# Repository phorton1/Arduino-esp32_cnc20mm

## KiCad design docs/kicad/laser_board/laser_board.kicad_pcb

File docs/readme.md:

# CNC Machine based on 20mm Stainless Steel Tubes

**Home** --
**[Design](design.md)** --
**[Details](details.md)** --
**[Electronics](electronics.md)** --
**[Box](box.md)** --
**[Spindle](spindle.md)** --
**[Y-Axis](y_axis.md)** --
**[Table](table.md)** --
**[Build](build.md)** --
**[Laser](laser.md)** --
**[Accessories](accessories.md)** --
**[Software](software.md)** --
**[Notes](notes.md)** --
**[Projects](projects.md)**

After completing the [2nd 3018](https://github.com/phorton1/Arduino-esp32_cnc3018/blob/master/docs/version2.md)
[cnc_machine](https://github.com/phorton1/Arduino-esp32_cnc3018), I felt I was
ready to attempt to make a larger machine.  I wanted to be able to cut 4x8 or 4x4 sheets
of plywood.

The belt driven cnc20mm machine is based on stainless steel 20mm tubes and 3D printed linear bearings that
utilize small inexpensive ball bearings.
It uses these items because it is prohibitively expensive to for me to ship large heavy items
like *aliminum extrusions* and *real linear bearings* and *linear drives* to my build location.
The biggest and heaviest parts are the lumber and stainless steel tubes,
both of which are available lococally.

The version I ended up building will cut a little bigger than 4x4 feet (51x50 inches).

It uses Nema23 motors.  These motors are larger than my previous machines
and so it requires larger, higher power, external controller boards.

## Outline of Documentation

On these pages I will *describe* and *show* the following:

- the basic mechanical **[Design](design.md)** of the machine
- some design **[Details](details.md)**, including Drag Chains, Connectors, etc
- the **[Electronics](electronics.md)** *Schematic* and *PCB* (Printed Circuit Board)
- the main **[Controller Box](box.md)**
- the separate **[Spindle](spindle.md)** controller box
- the *initial build* of the **[Y-Axis](y_axis.md)**
- constructing the **[Table](table.md)** (furniture) to support the machine
- assembling and **[Building](build.md)** the *actual* machine
- upgrading the **[Laser](laser.md)** from 500mw to a whopping **10W diode laser**
- adding **[Accessories](accessories.md)** including the *Spindle Controller* and *Vacuum* System
- installed and understanding the **[FluidNC Software](software.md)** for the *ESP32*
- implementation and historical **[Notes](notes.md)**
- and, finally, a few early **[Wooden Projects](projects.md)** that were made with the machine

## Materials available in this Repository

## Credits

R38 18x37 Drag Chain Model from Darko Saric Lukendic https://grabcad.com/library/cable-chain-18x37-1

## License

## Please Also See

- cnc3018
- vMachine
- FluidNC
- FluidNC_UI
- FluidNC_Extensions

**Next** - The basic [**Mechanical Design**](design.md) of the machine ...

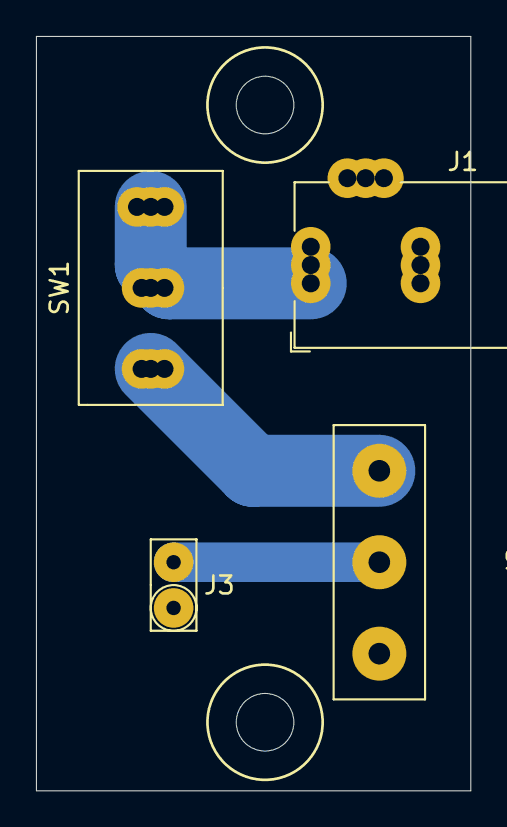
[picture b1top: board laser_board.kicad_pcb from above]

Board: 2 copper layers, 24.1 x 41.9 mm, 4 parts (0 on the bottom side), 4 nets.

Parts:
J1: Barrel_Jack_Switch; myBarrelJack
J2: Conn_01x03; Phoenix5.08x3
J3: Conn_01x02; my2pin
SW1: SW_SPDT; mySwitchToggleSPDT

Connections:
unnamed: J1.1, SW1.1, SW1.2
unnamed: J1.2, J2.3, J3.1
unnamed: J2.1, SW1.3
unnamed: J2.2, J3.2

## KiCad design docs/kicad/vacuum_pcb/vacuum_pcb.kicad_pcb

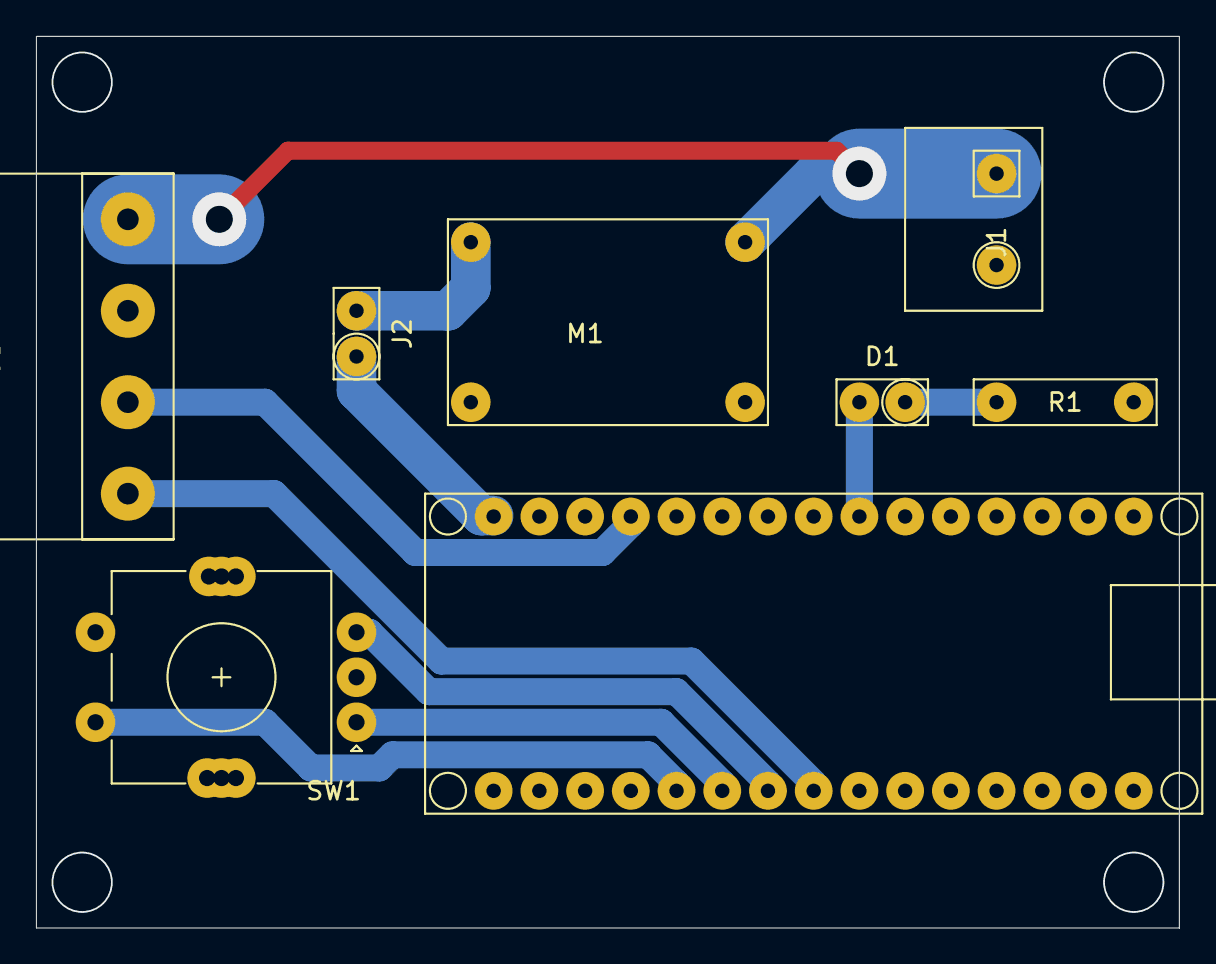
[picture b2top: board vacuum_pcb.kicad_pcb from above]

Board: 2 copper layers, 63.5 x 49.5 mm, 8 parts (0 on the bottom side), 11 nets.

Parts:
D1: LED; my2pin
J1: 24v; mySkip1
J2: 5V Jumper; my2pin
J3: Conn_01x04; big_4pin
M1: BUCK01
R1: 220; myResistor
SW1: RE; RotaryEncoder
U1: ARDUINO_NANO

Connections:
GND: J1.2, J3.3, M1.1, M1.2, R1.2, SW1.C, SW1.S2, U1.2, U1.27
unnamed: D1.1, R1.1
unnamed: D1.2, U1.9
unnamed: J1.1, J3.4, M1.4
unnamed: J2.1, U1.1
unnamed: J2.2, M1.3
unnamed: J3.1, U1.23
unnamed: J3.2, U1.4
unnamed: SW1.A, U1.25
unnamed: SW1.B, U1.24
unnamed: SW1.S1, U1.26

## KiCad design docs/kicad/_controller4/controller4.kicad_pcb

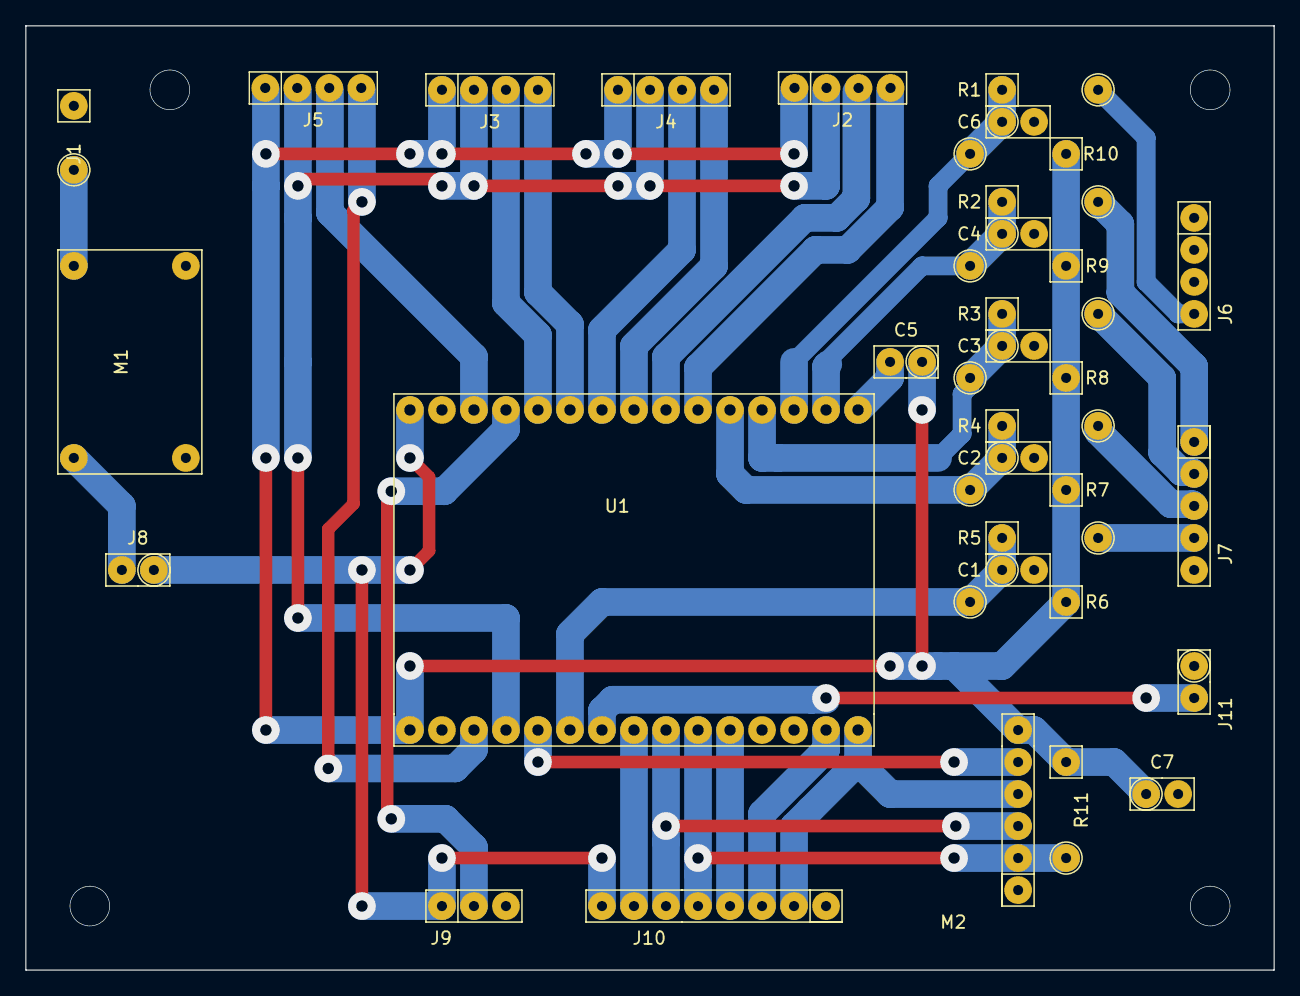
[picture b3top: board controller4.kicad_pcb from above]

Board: 2 copper layers, 99.1 x 74.9 mm, 32 parts (0 on the bottom side), 34 nets.

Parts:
C1, C2, C3, C4, C6: 100nf; my2pin
C5: 10uF; my2pin
C7: 220uf 10V; my2pin
J1: 24V; mySkip1
J2: Z_AXIS; my4pin
J3: A_AXIS; my4pin
J4: Y_AXIS; my4pin
J5: X_AXIS; my4pin
J6: PROBE; my4pin
J7: LIMITS; my5Pin
J8: USB 5V; my2pin
J9: LEDS; my3pin
J10: DISPLAY; my8Pin
J11: PWM; my2pin
M1: BUCK01
M2: SD CARD; my6Pin
R1, R2, R3, R4, R5: 100; mySkip2
R6, R7, R8, R9, R10, R11: 10K; mySkip2
U1: ESP32_DEV_0; ESP32-DEV_0

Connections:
+3V3: C5.1, C7.1, J2.1, J3.1, J4.1, J5.1, M2.6, R6.1, R7.1, R8.1, R9.1, R10.1, R11.1, U1.30
+5V: J8.1, J9.1, J10.8, U1.1
A_DIR: J3.3, U1.5
A_STEP: J3.4, U1.6
A_SW: C3.1, R3.1, R8.2, U1.12
GND: C1.2, C2.2, C3.2, C4.2, C6.2, C7.2, J1.1, J7.5, J9.3, J10.1, J11.1, M1.1, M1.2, M2.1, U1.2, U1.29
LED: J9.2, U1.4
MCLK: J10.6, M2.3, U1.22
MISO: J10.5, M2.2, R11.2, U1.21
MOSI: J10.2, M2.4, U1.16
unnamed: C5.2, U1.15
unnamed: J1.2, M1.4
unnamed: J6.4, R1.2
unnamed: J7.1, R2.2
unnamed: J7.2, R3.2
unnamed: J7.3, R4.2
unnamed: J7.4, R5.2
unnamed: J8.2, M1.3
PROBE_SW: C6.1, R1.1, R10.2, U1.13
PWM: J11.2, U1.24
SD_CS: M2.5, U1.26
STEP_EN: J2.2, J3.2, J4.2, J5.2, U1.27
TFT_CS: J10.3, U1.17
TFT_DC: J10.4, U1.20
TOUCH_CS: J10.7, U1.23
X_DIR: J2.3, U1.9
X_STEP: J2.4, U1.10
X_SW: C1.1, R5.1, R6.2, U1.25
Y_DIR: J4.3, U1.7
Y_STEP: J4.4, U1.8
Y_SW: C2.1, R4.1, R7.2, U1.11
Z_DIR: J5.3, U1.3
Z_STEP: J5.4, U1.28
Z_SW: C4.1, R2.1, R9.2, U1.14

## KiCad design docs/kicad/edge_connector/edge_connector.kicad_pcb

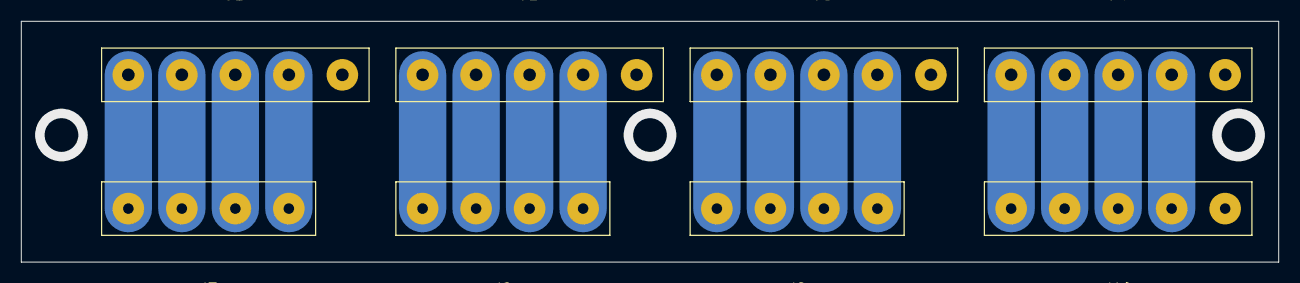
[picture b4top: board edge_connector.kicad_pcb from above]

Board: 2 copper layers, 119.4 x 22.9 mm, 8 parts (0 on the bottom side), 17 nets.

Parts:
J1, J2, J3, J4, J10: Conn_01x05; big_5pin
J7, J8, J9: Conn_01x04; big_4pin

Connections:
GND: J1.5, J2.5, J3.5, J4.5, J10.1
unnamed: J1.1, J7.4
unnamed: J1.2, J7.3
unnamed: J1.3, J7.2
unnamed: J1.4, J7.1
unnamed: J2.1, J8.4
unnamed: J2.2, J8.3
unnamed: J2.3, J8.2
unnamed: J2.4, J8.1
unnamed: J3.1, J9.4
unnamed: J3.2, J9.3
unnamed: J3.3, J9.2
unnamed: J3.4, J9.1
unnamed: J4.4, J10.2
unnamed: J4.3, J10.3
unnamed: J4.2, J10.4
unnamed: J4.1, J10.5

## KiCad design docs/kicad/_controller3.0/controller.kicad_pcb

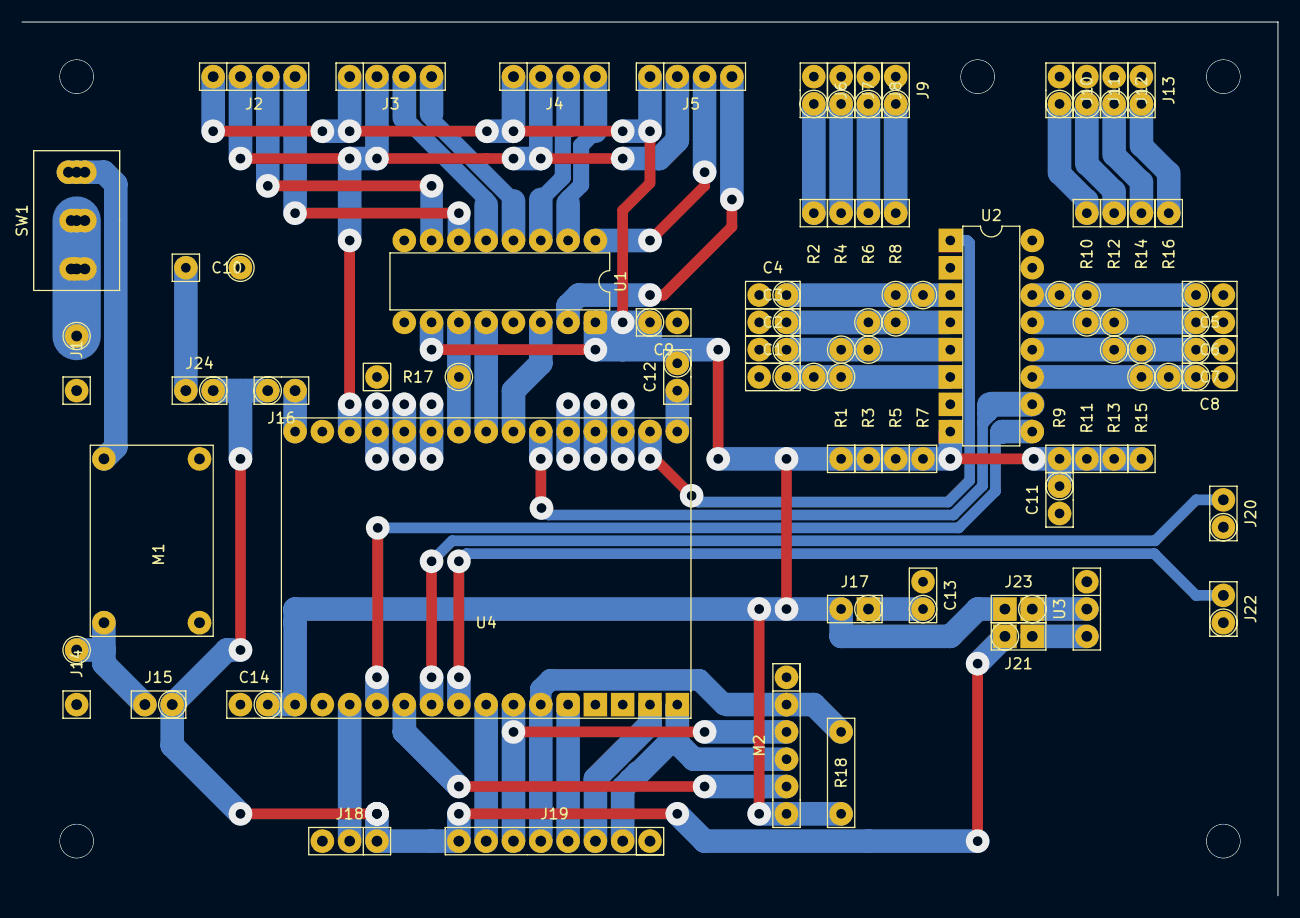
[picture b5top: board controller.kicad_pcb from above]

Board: 2 copper layers, 116.8 x 81.3 mm, 63 parts (0 on the bottom side), 53 nets.

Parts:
C1, C2, C3, C4, C5, C6, C7, C8, C9, C11, C14: 100nf; my2pin
C10: 330uf 50v; mySkip1
C12: 10uF; my2pin
C13: 220uf 10V; my2pin
J1: 24V; mySkip1
J2: X_AXIS; my4pin
J3: A_AXIS; my4pin
J4: Y_AXIS; my4pin
J5: Z_AXIS; my4pin
J6: X_ZERO; my2pin
J7: X_LIM; my2pin
J8: Y_ZERO; my2pin
J9: Y_LIM; my2pin
J10: Z_ZERO; my2pin
J11: Z_LIM; my2pin
J12: PROBE; my2pin
J13: UNUSED; my2pin
J14: 5V; mySkip1
J15: EXT 5V; my2pin
J16: USB 5V; my2pin
J17: CAP3V; my2pin
J18: WS2812B Strip; my3pin
J19: Display; my8Pin
J20: PWM_1A; my2pin
J21: REG5V; my2pin
J22: PWM_2A; my2pin
J23: REG3V; my2pin
J24: CAP5V; my2pin
M1: BUCK01
M2: SD_TYP0; my6Pin
R1, R15, R17: 10K; mySkip2
R2, R16: 100; mySkip5
R3, R13: 10K; mySkip3
R4, R14: 100; mySkip4
R5, R11: 10K; mySkip4
R6, R12: 100; mySkip3
R7, R9: 10K; mySkip5
R8, R10: 100; mySkip2
R18: 10K; myResistor
SW1: POWER; SW_DPDT_BLUE_LEVER
U1: 74HC595; myDip16
U2: 74HC165; myDip16
U3: LM1117; my3pin
U4: ESP32_DEV_0; ESP32-DEV_0

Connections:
+3V3: C9.1, C11.1, C12.1, C14.1, J2.1, J3.1, J4.1, J5.1, J17.2, J23.2, M2.6, R1.1, R3.1, R5.1, R7.1, R9.1, R11.1, R13.1, R15.1, R18.1, U1.10, U1.16, U2.8, U4.30
+5V: J15.1, J16.1, J18.1, J19.8, J21.1, J24.1
+24V: M1.4, SW1.1
A_DIR: J3.3, U1.5
A_STEP: J3.4, U1.4
GND: C1.2, C2.2, C3.2, C4.2, C5.2, C6.2, C7.2, C8.2, C9.2, C10.2, C11.2, C13.2, C14.2, J1.1, J6.2, J7.2, J8.2, J9.2, J10.2, J11.2, J12.2, J13.2, J14.1, J18.3, J19.1, J20.1, J22.1, M1.1, M1.2, M2.1, R17.1, U1.8, U1.13, U2.2, U2.7, U2.16, U3.1, U4.2, U4.29
I2S_BCK: R17.2, U1.11, U4.7
I2S_DATA: U1.14, U4.9
I2S_WS: U1.12, U4.8
LED: J18.2, U4.28
MCLK: J19.6, M2.3, U4.22
MISO: J19.5, M2.2, R18.2, U4.21
MOSI: J19.2, M2.4, U4.16
unnamed: C1.1, R1.2, R2.2, U2.6
unnamed: C2.1, R3.2, R4.2, U2.5
unnamed: C3.1, R5.2, R6.2, U2.4
unnamed: C4.1, R7.2, R8.2, U2.3
unnamed: C5.1, R9.2, R10.2, U2.14
unnamed: C6.1, R11.2, R12.2, U2.13
unnamed: C7.1, R13.2, R14.2, U2.12
unnamed: C8.1, R15.2, R16.2, U2.11
unnamed: C10.1, J24.2
unnamed: C12.2, U4.15
unnamed: C13.1, J17.1
unnamed: J1.2, SW1.2, SW1.3
unnamed: J6.1, R2.1
unnamed: J7.1, R4.1
unnamed: J8.1, R6.1
unnamed: J9.1, R8.1
unnamed: J10.1, R10.1
unnamed: J11.1, R12.1
unnamed: J12.1, R14.1
unnamed: J13.1, R16.1
unnamed: J14.2, J15.2, M1.3
unnamed: J16.2, U4.1
unnamed: J21.2, U3.3
unnamed: J23.1, U3.2
PWM_1: J20.2, U4.25
PWM_2: J22.2, U4.24
SD_CS: M2.5, U4.26
STEP_EN: J2.2, J3.2, J4.2, J5.2, U4.3
SW_CLK: U2.10, U4.10
SW_DATA: U2.1, U4.14
SW_LATCH: U2.9, U4.27
TFT_CS: J19.3, U4.17
TFT_DC: J19.4, U4.20
TOUCH_CS: J19.7, U4.23
X_DIR: J2.3, U1.7
X_STEP: J2.4, U1.6
Y_DIR: J4.3, U1.3
Y_STEP: J4.4, U1.2
Z_DIR: J5.3, U1.1
Z_STEP: J5.4, U1.15

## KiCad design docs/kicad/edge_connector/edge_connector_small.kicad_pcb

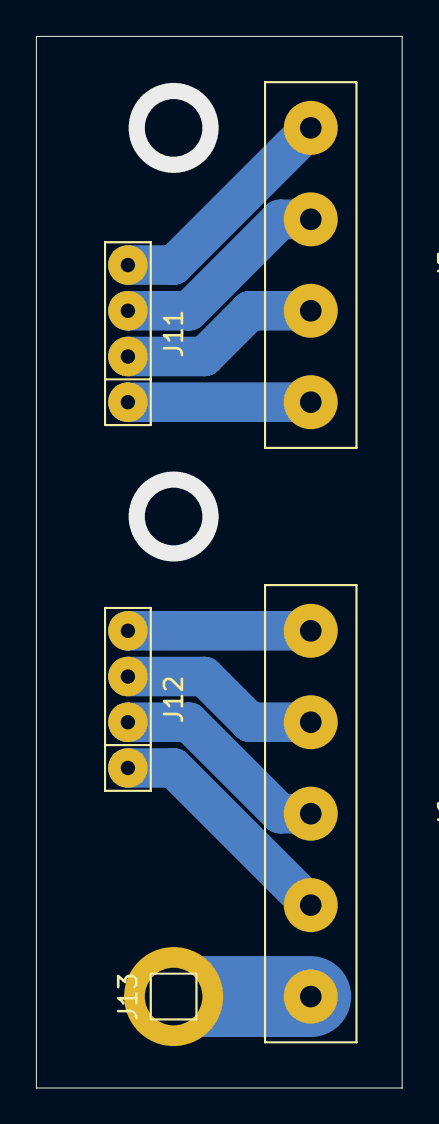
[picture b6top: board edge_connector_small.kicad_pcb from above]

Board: 2 copper layers, 20.3 x 58.4 mm, 5 parts (0 on the bottom side), 9 nets.

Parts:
J5: Conn_01x04; big_4pin
J6: Conn_01x05; big_5pin
J11, J12: Conn_01x04; my4pin
J13: Conn_01x01; my1pin

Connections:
unnamed: J5.4, J11.1
unnamed: J5.3, J11.2
unnamed: J5.2, J11.3
unnamed: J5.1, J11.4
unnamed: J6.4, J12.1
unnamed: J6.3, J12.2
unnamed: J6.2, J12.3
unnamed: J6.1, J12.4
unnamed: J6.5, J13.1

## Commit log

2022-03-28 initial commit (from branch)
2022-03-28 rename files, initial build
2022-04-10 renamed config_v3_i2s0.yaml to config_cnc20mm.yaml, noting that the laser and non-laser are the same (as long as I have no PWM spindle)
2022-04-10 sanity checking after completing most circuit boards
2022-04-13 added spindle connector kicad stuff
2022-04-13 added stepper wiring and full cnc pin_history (comments only)
2022-04-14 remove vTaskDelay that was kludge for logging synchronization
2022-04-14 comments only
2022-04-15 implement FluidNC_UI driver/size/rotation API - rename tft calibration data files
2022-04-15 Implement LIMIT_PINS and REVERSE_PIXELS
2022-04-18 Initial readme.md, pics, and two youtube videos
2022-04-18 readme
2022-05-19 change big edge connector to 5 pin (grounds for steppers)
2022-05-23 added tasks.txt - analsysis of running tasks
2022-07-03 update prefs for build
2022-07-03 use 32bit limit variables, set XYAZ orcer
2022-07-03 final INITIAL WORKING CNC20MM
2022-07-05 added laser_board
2022-07-05 cleanup configs (add Laser)
2022-07-05 updated preferences.txt
2022-07-05 correct probe pin
2022-07-21 added #ifdef'd out WEAK_LINK display() method
2022-07-29 Turned off DEBUG_PIXELS define
2022-07-29 sdded disasm_cmd.bat to get disassembly listings for debugging
2022-07-29 changed (fixed) WEAK_LINK display() method (though it still doesnt work with UGS)
2022-07-29 changed PWM_HZ to 5000 which fixed some laser missing bands
2022-08-09 new controller4 (v4) circuit board
2022-08-09 NEW v4 CONFIG FILE
2022-08-10 add v4 comments
2022-08-21 added ToolChange macro files
2022-08-21 added comments on how to run toolChange macros from SPIFFS
2022-08-21 added setting_z_height.txt document
2022-08-24 better TOOL CHANGE macros - got rid of analysis
2022-08-24 lower homing feed rates
2022-12-12 updated ground plane while reviewing docs and pcbs
2023-03-21 make the current v4 configuration the default config.yaml
2023-04-16 moved to /bat
2023-07-17 docs - start writing actual documentation
2023-07-17 doc - typos
2023-07-20 docs - work on design.md
2023-07-21 docs - post production materials, rework designs for publication
2023-07-22 docs - completed redesign, ready to start working on docs again
2023-07-24 docs - rework whole fusion design
2023-07-25 docs - cleanup stl & gcode for publication
2023-07-26 docs - design DETAILS and SPINDLE pages
2023-07-27 docs - fleshed out the TABLE, Y-AXIS, and BUILD pages
2023-07-27 docs - fleshed out LASER and ACESSORIES pages
2023-07-28 docs - added Laser Board to laser page
2023-07-28 rename and comment titles of yaml files
2023-07-28 docs - start SOFTWARE page
2023-07-28 docs - finish SOFTWARE page includig TASK ANALYSIS
2023-10-10 added LICENSE.TXT and empty docs/readme.md to most public repositories
2023-11-02 fix broken links across all repos with introduction of base-apps-gitUI::repoDocs.pm
